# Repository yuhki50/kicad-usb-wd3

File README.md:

# USB WD3

## Board specifications

* Layer: 2
* Dimensions: 43.5 x 28.5 mm
* PCB Thickness: 1.0 mm
* PCB Color: Green
* Surface Finish: HASL Lead Free
* Castellated Hole: No
* Copper Weight:1oz

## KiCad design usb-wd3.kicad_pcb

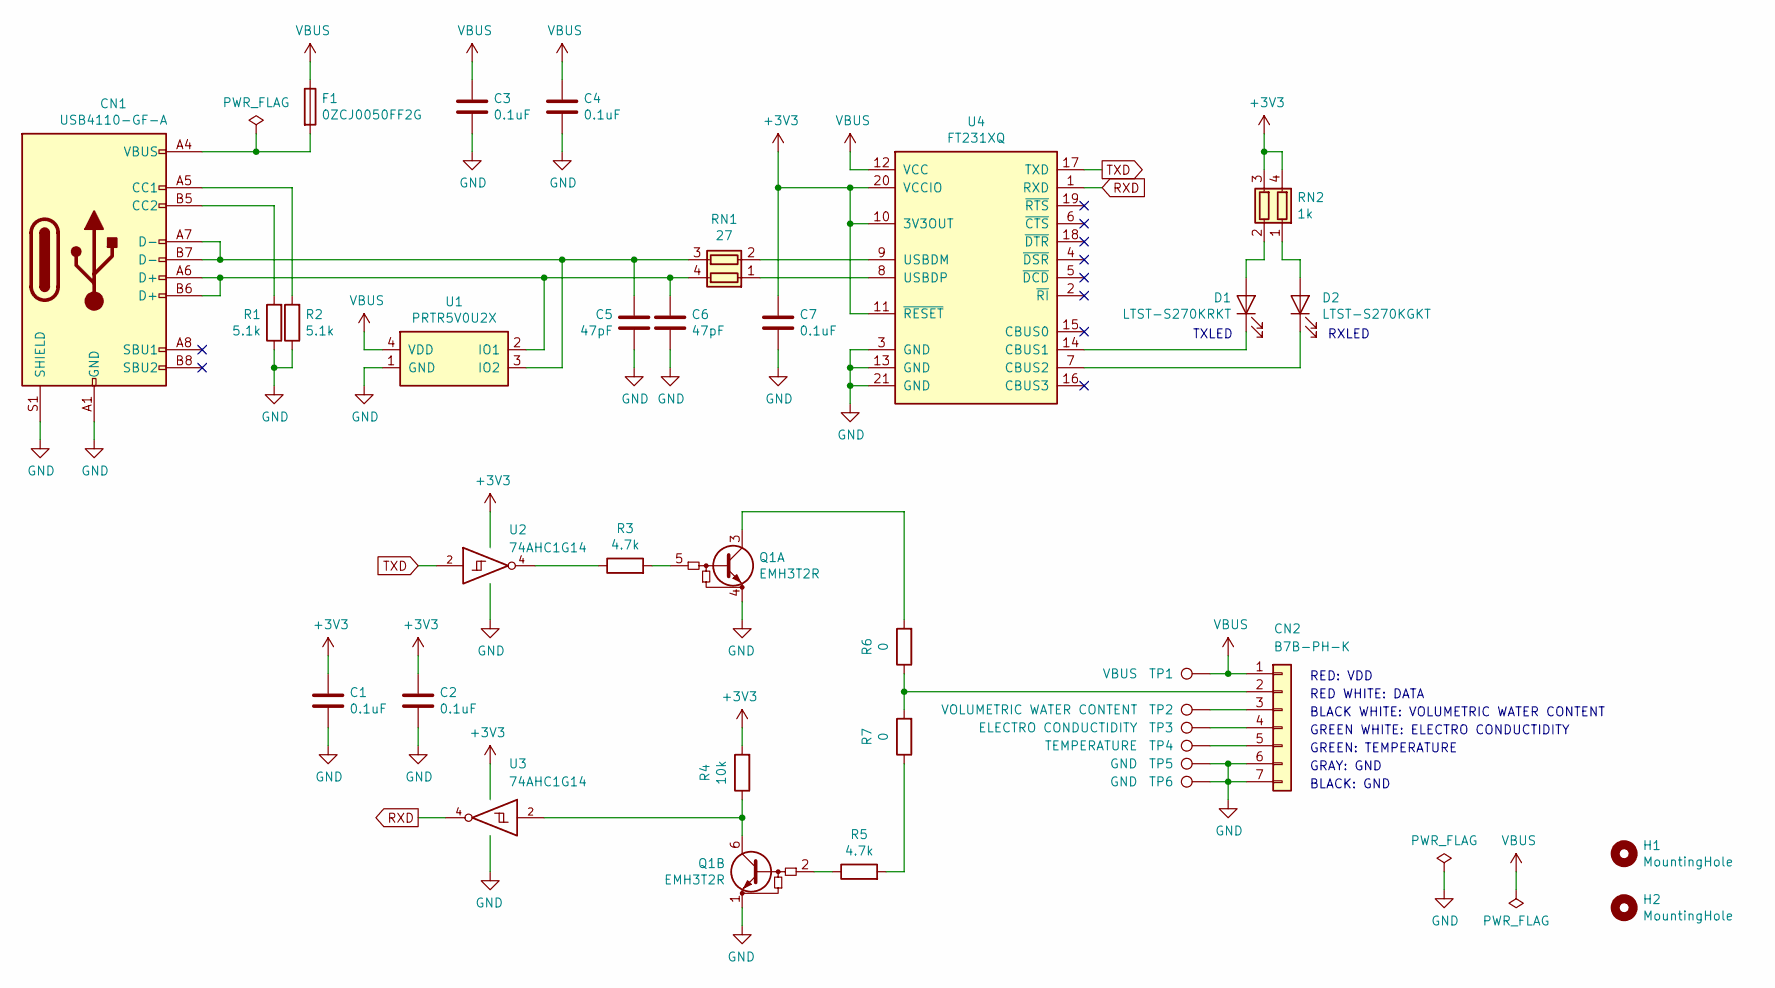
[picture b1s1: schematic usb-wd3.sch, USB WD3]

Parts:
C1, C2, C3, C4, C7: 0.1uF; C_0402_1005Metric
C5, C6: 47pF; C_0402_1005Metric
CN1: USB4110-GF-A
CN2: B7B-PH-K; JST_PH_B7B-PH-K_1x07_P2.00mm_Vertical
D1: LTST-S270KRKT; LED_0603_1608Metric
D2: LTST-S270KGKT; LED_0603_1608Metric
F1: 0ZCJ0050FF2G; Fuse_1206_3216Metric
H1, H2: MountingHole; MountingHole_2.2mm_M2
Q1: EMH3T2R; SOT-563
R1, R2: 5.1k; R_0402_1005Metric
R3, R5: 4.7k; R_0402_1005Metric
R4: 10k; R_0402_1005Metric
R6, R7: 0; R_0402_1005Metric
RN1: 27; R_Array_Convex_2x0402
RN2: 1k; R_Array_Convex_2x0402
TP1: VBUS; TestPoint_Pad_D2.0mm
TP2: VOLUMETRIC WATER CONTENT; TestPoint_Pad_D2.0mm
TP3: ELECTRO CONDUCTIDITY; TestPoint_Pad_D2.0mm
TP4: TEMPERATURE; TestPoint_Pad_D2.0mm
TP5, TP6: GND; TestPoint_Pad_D2.0mm
U1: PRTR5V0U2X; SOT-143B
U2, U3: 74AHC1G14; SOT-353_SC-70-5
U4: FT231XQ; QFN-20-1EP_4x4mm_P0.5mm_EP2.5x2.5mm

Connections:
+3V3: C1.2, C2.2, C7.2, R4.2, RN2.3 (R2.2), RN2.4 (R1.2), U2.5 (VCC), U3.5 (VCC), U4.10 (3V3OUT), U4.11 (~RESET), U4.20 (VCCIO)
GND: C1.1, C2.1, C3.2, C4.2, C5.2, C6.2, C7.1, CN1.A1 (GND), CN1.A12 (GND), CN1.B1 (GND), CN1.B12 (GND), CN1.S1 (SHIELD), CN2.6, CN2.7, Q1.1 (E1), Q1.4 (E1), R1.1, R2.1, TP5.1, TP6.1, U1.1 (GND), U2.3 (GND), U3.3 (GND), U4.3 (GND), U4.13 (GND), U4.21 (GND)
unnamed: C5.1, CN1.A7 (D-), CN1.B7 (D-), RN1.3 (R2.2), U1.3 (IO2)
unnamed: C6.1, CN1.A6 (D+), CN1.B6 (D+), RN1.4 (R1.2), U1.2 (IO1)
unnamed: CN1.A4 (VBUS), CN1.A9 (VBUS), CN1.B4 (VBUS), CN1.B9 (VBUS), F1.2
unnamed: CN1.A5 (CC1), R2.2
unnamed: CN1.B5 (CC2), R1.2
unnamed: CN2.2, R6.1, R7.2
unnamed: CN2.3, TP2.1
unnamed: CN2.4, TP3.1
unnamed: CN2.5, TP4.1
unnamed: D1.1 (K), U4.14 (CBUS1)
unnamed: D1.2 (A), RN2.2 (R2.1)
unnamed: D2.1 (K), U4.7 (CBUS2)
unnamed: D2.2 (A), RN2.1 (R1.1)
unnamed: Q1.2 (B1), R5.1
unnamed: Q1.3 (C1), R6.2
unnamed: Q1.5 (B1), R3.2
unnamed: Q1.6 (C1), R4.1, U3.2
unnamed: R3.1, U2.4
unnamed: R5.2, R7.1
unnamed: RN1.1 (R1.1), U4.8 (USBDP)
unnamed: RN1.2 (R2.1), U4.9 (USBDM)
RXD: U3.4, U4.1 (RXD)
TXD: U2.2, U4.17 (TXD)
VBUS: C3.1, C4.1, CN2.1, F1.1, TP1.1, U1.4 (VDD), U4.12 (VCC)

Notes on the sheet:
RXLED
TXLED
BLACK WHITE: VOLUMETRIC WATER CONTENT
GREEN WHITE: ELECTRO CONDUCTIDITY
GREEN: TEMPERATURE
BLACK: GND
GRAY: GND
RED: VDD
RED WHITE: DATA

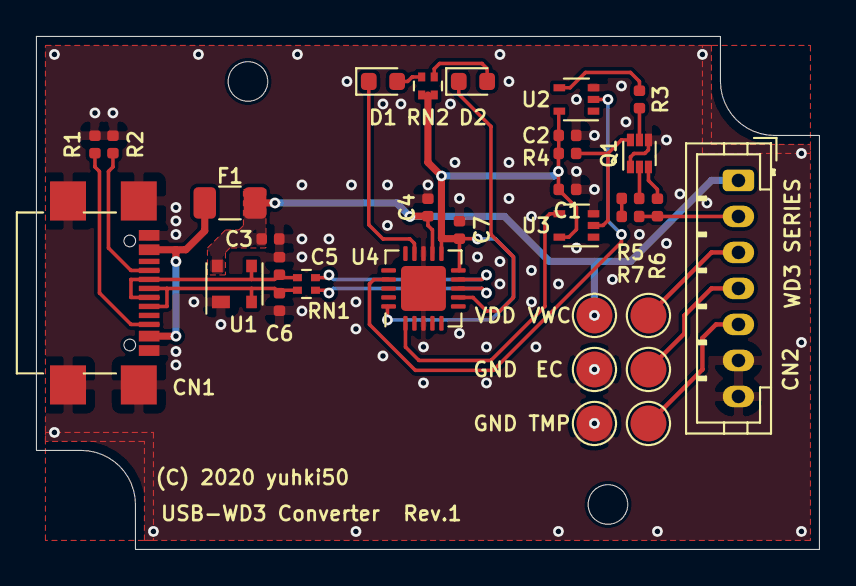
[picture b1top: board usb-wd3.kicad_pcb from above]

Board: 2 copper layers, 43.5 x 28.5 mm, 34 parts (0 on the bottom side), 26 nets.

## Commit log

2020-04-26 Add gitignore
2020-04-26 Create project using KiCad (v5.1.5-0-10_14)
2020-04-26 Add library, modules
2020-04-26 Implement
2020-04-26 Add README

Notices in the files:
usb-wd3.kicad_pcb:
(C) 2020 yuhki50
